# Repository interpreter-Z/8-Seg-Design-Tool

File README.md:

# 8-Seg-Design-Tool
A PCB click-toy that you can use to design 8-segment display patterns (or kill time with)

This repo houses a simple hardware project for a custom PCB designed with KiCad 6.0.

For more information on the following items, please refer to:
- Final product:      README.pdf
- PCB source files:   8 Seg Design Tool/
- Gerber files:       gerbers/
- Components:         datasheet/
- Purchase Links:     BOM.csv

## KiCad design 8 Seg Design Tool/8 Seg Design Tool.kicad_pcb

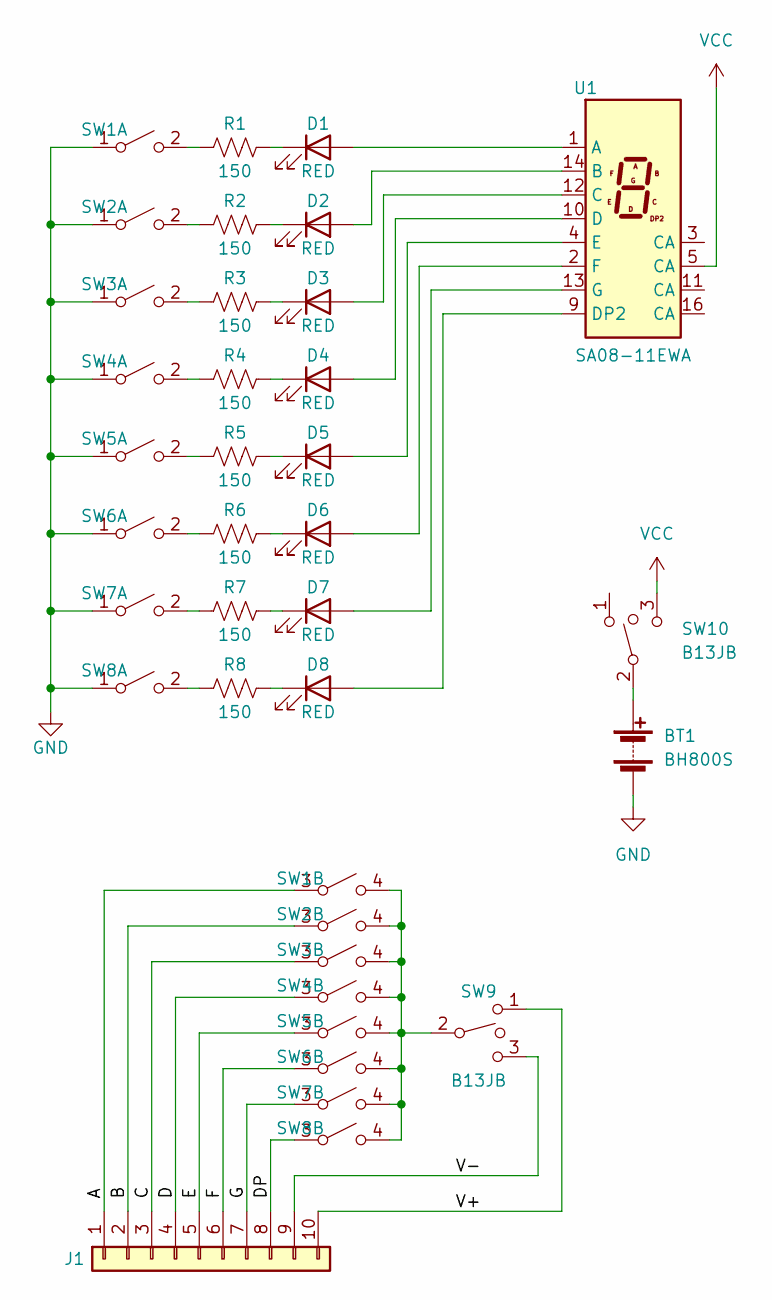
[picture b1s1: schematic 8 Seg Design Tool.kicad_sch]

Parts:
BT1: BH800S
D1, D2, D3, D4, D5, D6, D7, D8: RED; LS-L29K-G1J2-1-Z
J1: Conn_01x10; 613010143121
R1, R2, R3, R4, R5, R6, R7, R8: 150; RMCF1206JT150R
SW1, SW2, SW3, SW4, SW5, SW6, SW7, SW8: SW_DPST_x2; PVA1EEH11-2NV2-PDIP
SW9, SW10: B13JB
U1: SA08-11EWA; SA08-11EWA-PDIP

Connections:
GND: BT1.2 (-), SW1.1 (A), SW2.1 (A), SW3.1 (A), SW4.1 (A), SW5.1 (A), SW6.1 (A), SW7.1 (A), SW8.1 (A)
unnamed: BT1.1 (+), SW10.2 (B)
unnamed: D1.1 (K), R1.2
unnamed: D1.2 (A), U1.1 (A)
unnamed: D2.1 (K), R2.2
unnamed: D2.2 (A), U1.14 (B)
unnamed: D3.1 (K), R3.2
unnamed: D3.2 (A), U1.12 (C)
unnamed: D4.1 (K), R4.2
unnamed: D4.2 (A), U1.10 (D)
unnamed: D5.1 (K), R5.2
unnamed: D5.2 (A), U1.4 (E)
unnamed: D6.1 (K), R6.2
unnamed: D6.2 (A), U1.2 (F)
unnamed: D7.1 (K), R7.2
unnamed: D7.2 (A), U1.13 (G)
unnamed: D8.1 (K), R8.2
unnamed: D8.2 (A), U1.9 (DP2)
unnamed: J1.1, SW1.3 (A)
unnamed: J1.2, SW2.3 (A)
unnamed: J1.3, SW3.3 (A)
unnamed: J1.4, SW4.3 (A)
unnamed: J1.5, SW5.3 (A)
unnamed: J1.6, SW6.3 (A)
unnamed: J1.7, SW7.3 (A)
unnamed: J1.8, SW8.3 (A)
unnamed: J1.9, SW9.3 (C)
unnamed: J1.10, SW9.1 (A)
unnamed: R1.1, SW1.2 (B)
unnamed: R2.1, SW2.2 (B)
unnamed: R3.1, SW3.2 (B)
unnamed: R4.1, SW4.2 (B)
unnamed: R5.1, SW5.2 (B)
unnamed: R6.1, SW6.2 (B)
unnamed: R7.1, SW7.2 (B)
unnamed: R8.1, SW8.2 (B)
unnamed: SW1.4 (B), SW2.4 (B), SW3.4 (B), SW4.4 (B), SW5.4 (B), SW6.4 (B), SW7.4 (B), SW8.4 (B), SW9.2 (B)
VCC: SW10.3 (C), U1.5 (CC)

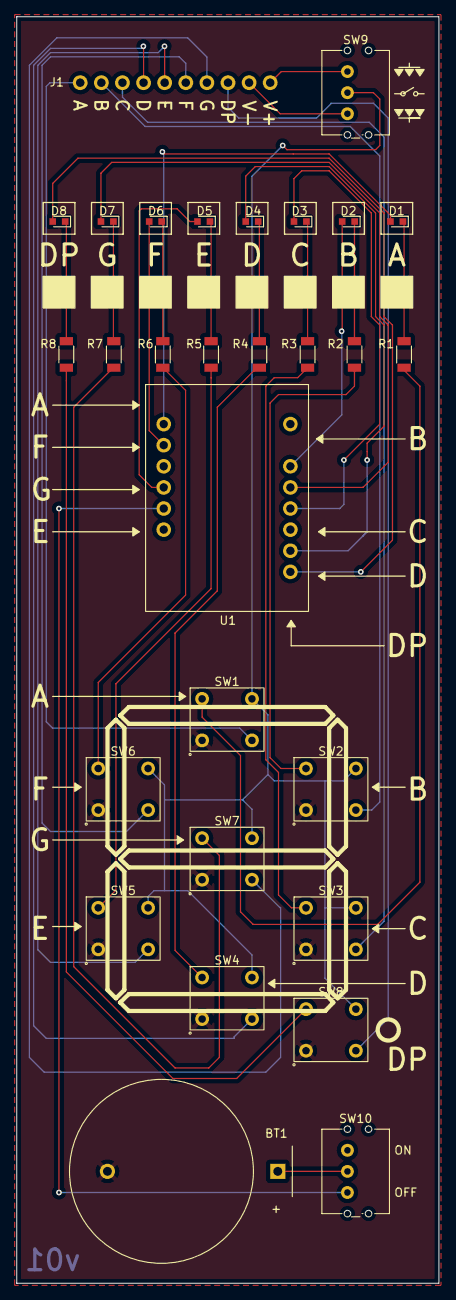
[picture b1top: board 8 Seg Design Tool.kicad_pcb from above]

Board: 2 copper layers, 50.8 x 152.4 mm, 29 parts (0 on the bottom side), 38 nets.

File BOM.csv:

Source:,D:\SPTS_A\MyWorks\KiCad\8 Seg Design Tool\8 Seg Design Tool\8 Seg Design Tool.kicad_sch,,,,,,,,,
Date:,6/13/2022 00:46,,,,,,,,,
Tool:,Eeschema (6.0.0),,,,,,,,,
Generator:,D:\SPTS_B\Applications\KiCad\6.0\bin\scripting\plugins/bom_csv_grouped_by_value.py,,,,,,,,,
Component Count:,29,,,,,,,,,
,,,,,,,,,,
Collated Components:,,,,,,,,,,
,,,,,,,,,,
Num Duplicates,2,,,,,(At 1 Dup),,(At Dup Qty),,
Item,Qty,Dup Qty,Reference(s),Value,MPN,Unit Price,Total Price,Unit Price,Total Price,URL
1,1,2,BT1,BH800S,BH800S,$1.41 ,$1.41 ,$1.41 ,$2.82 ,https://www.digikey.com/en/products/detail/mpd-memory-protec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
2,8,16,"D1, D2, D3, D4, D5, D6, D7, D8",RED,LS L29K-G1J2-1-Z,$0.41 ,$3.28 ,$0.32 ,$5.14 ,https://www.digikey.com/en/products/detail/osram-opto-semico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
3,1,2,J1,Conn_01x10,6.1301E+11,$0.95 ,$0.95 ,$0.95 ,$1.90 ,https://www.digikey.com/en/products/detail/w%C3%BCrth-elektr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
4,8,16,"R1, R2, R3, R4, R5, R6, R7, R8",150,RMCF1206JT150R,$0.10 ,$0.80 ,$0.03 ,$0.45 ,https://www.digikey.com/en/products/detail/stackpole-electro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
5,8,16,"SW1, SW2, SW3, SW4, SW5, SW6, SW7, SW8",SW_DPST_x2,PVA1EEH11.2NV2,$1.65 ,$13.20 ,$1.48 ,$23.63 ,https://www.digikey.com/en/products/detail/c-k/PVA1EEH11-2NV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
6,2,4,"SW9, SW10",B13JB,B13JB,$4.92 ,$9.84 ,$4.92 ,$19.68 ,https://www.digikey.com/en/products/detail/nkk-switches/B13J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
7,1,2,U1,SA08-11EWA,CDSA15R1W,$2.98 ,$2.98 ,$2.98 ,$5.96 ,https://www.digikey.com/en/products/detail/chromeled/CDSA15R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
8,1,10,-,-,CR2025,$0.32 ,$0.32 ,$0.26 ,$2.64 ,https://www.digikey.com/en/products/detail/murata-electronic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
,,,,,,,,,,
,,,,,,Total:,$32.78 ,Total:,$62.22 ,

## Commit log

2022-08-14 TEST
2022-08-14 inital batch upload
2022-08-14 upload kicad bkup

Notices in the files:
8 Seg Design Tool/8 Seg Design Tool.kicad_pcb:
https://creativecommons.org/licenses/by/4.0
License: CC BY 4.0
